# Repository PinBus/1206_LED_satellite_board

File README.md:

# 1206 LED Satellite Board - Rev. 1.0

This board is designed for three 1206 SMD LEDs. It can be used with the [TLC5940 LED Driver Board](https://github.com/PinBus/TLC5940_LED_driver_board). The LEDs are connected in series.

Replace the 0Ω resistor R0 when not using a LED driver IC. You can use any colour of LED for D1, D2, and D3.

**Warning: These designs are made as part of a hobby project and thus come with no guarantees. Do not use these designs in for any critical systems! Working with voltages higher than +40V can be potentially dangerous, please take appropriate safety measures!**

## BOM

| Identifiers | Quantity | Part |
| ----------- | -------- | ---- |
| J1          |       1x | JST XH connector, 2.5mm pitch, 2-way, through hole |
| R1          |       1x | 1206 SMD 0Ω resistor |
| D1, D2, D3  |       3x | 1206 SMD LED |

## Pictures

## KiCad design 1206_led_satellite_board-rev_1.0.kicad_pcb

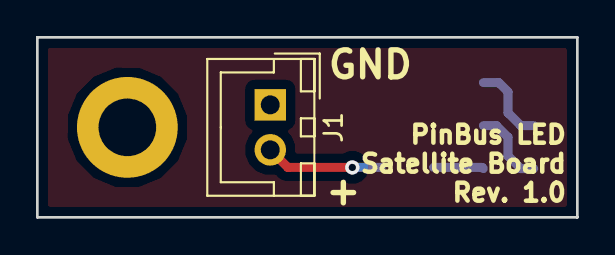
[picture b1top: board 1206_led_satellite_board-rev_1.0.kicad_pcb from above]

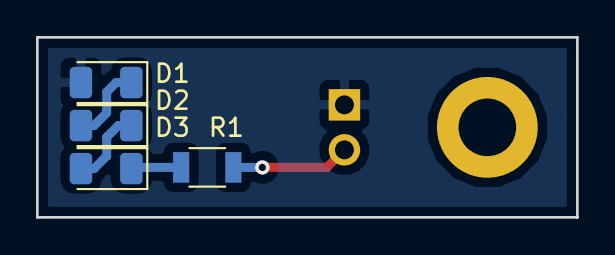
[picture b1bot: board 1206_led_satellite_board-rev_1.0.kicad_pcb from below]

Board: 2 copper layers, 30.0 x 10.0 mm, 5 parts (4 on the bottom side), 5 nets.

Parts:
D1, D2, D3: LED; LED_1206_3216Metric
J1: Conn_01x02_Male; JST_XH_B02B-XH-A_02x2.50mm_Straight
R1: 0R; R_1206

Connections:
unnamed: D1.1, D2.2
unnamed: D1.2, J1.1
unnamed: D2.1, D3.2
unnamed: D3.1, R1.1
unnamed: J1.2, R1.2

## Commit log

2018-12-13 Add hardware design files
2019-01-17 Improve documentation
